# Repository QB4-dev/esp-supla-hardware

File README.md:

# esp-supla-hardware
My SUPLA compatible boards

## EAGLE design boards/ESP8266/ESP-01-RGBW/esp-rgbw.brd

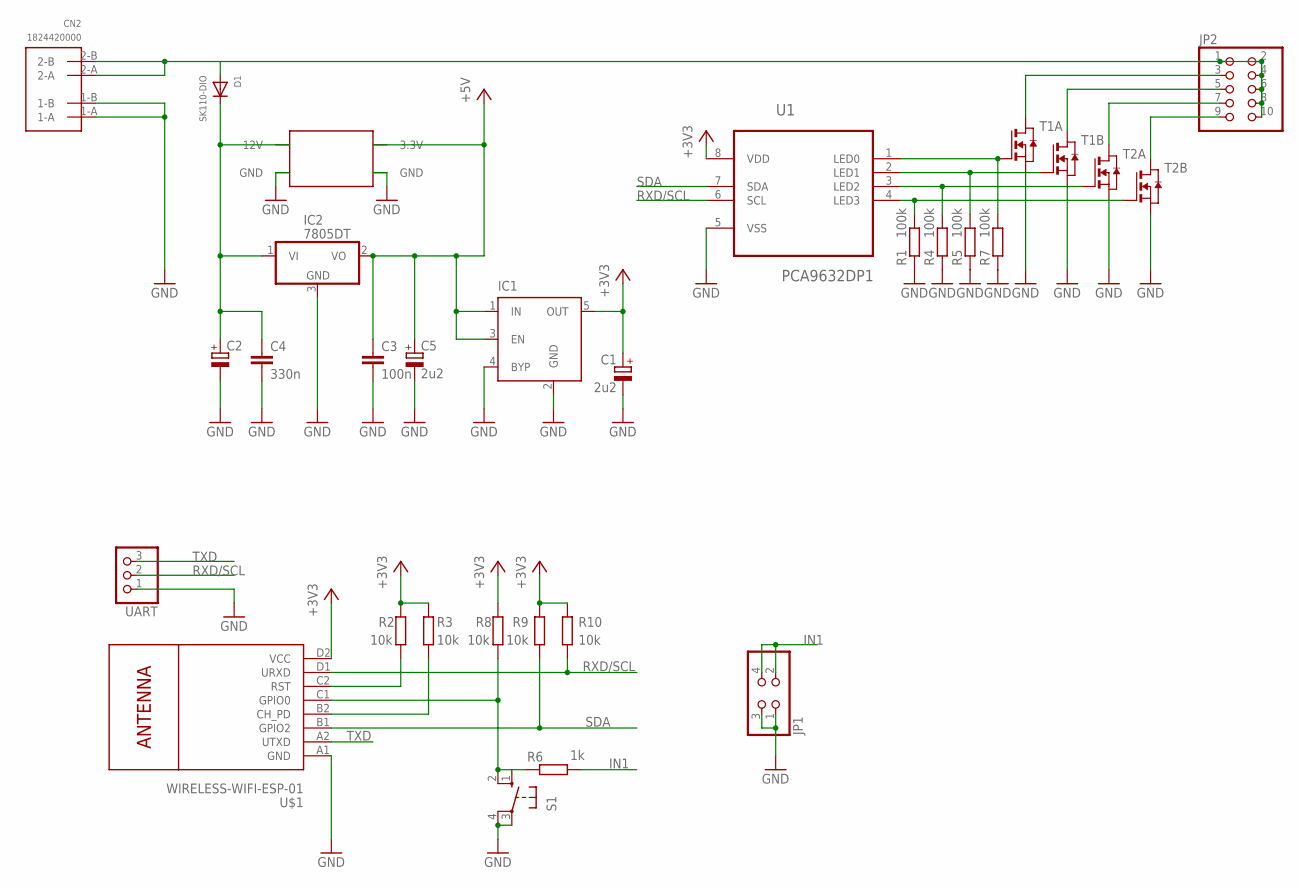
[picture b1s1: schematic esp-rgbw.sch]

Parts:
C1, C5: 2u2; SMC_B
C2: CPOL-EUC/6032-28R; C/6032-28R
C3: 100n; C0805
C4: 330n; C0805
CN2: 1824420000
D1: SK110-DIO; SMADIODE
IC1: MIC5219XX; SOT23-5
IC2: 7805DT; TO252
JP1: PINHD-2X2; 2X02
JP2: PINHD-2X5; 2X05
R1, R4, R5, R7: 100k; R0805
R2, R3, R8, R9, R10: 10k; R0805
R6: 1k; R0805
S1: 10-XX; B3F-10XX
T1, T2: NMOS2SO8; SO8
U1: PCA9632DP1; SOP65P490X110-8N
U$1: WIRELESS-WIFI-ESP-01
U$2: MP2307-MINI-360
UART: PINHD-1X3; 1X03

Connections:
+3V3: C1.+, IC1.5 (OUT), R2.2, R3.2, R8.2, R9.2, R10.2, U1.8 (VDD), U$1.D2 (VCC)
+5V: C3.1, C5.+, IC1.1 (IN), IC1.3 (EN), IC2.2 (VO), U$2.3.3V
GND: C1.-, C2.-, C3.2, C4.2, C5.-, CN2.1-A, CN2.1-B, IC1.2 (GND), IC1.4 (BYP), IC2.3 (GND), JP1.1, JP1.3, R1.1, R4.1, R5.1, R7.1, S1.3, S1.4 (P1), T1.1 (S), T1.3 (S), T2.1 (S), T2.3 (S), U1.5 (VSS), U$1.A1 (GND), U$2.GND@1 (GND), U$2.GND@2 (GND), UART.1
IN1: JP1.2, JP1.4, R6.1
unnamed: R3.1, U$1.B2 (CH_PD)
unnamed: R2.1, U$1.C2 (RST)
unnamed: R6.2, R8.1, S1.1 (S), S1.2 (S1), U$1.C1 (GPIO0)
unnamed: JP2.3, T1.7 (D), T1.8 (D)
unnamed: JP2.5, T1.5 (D), T1.6 (D)
unnamed: C2.+, C4.1, D1.C, IC2.1 (VI), U$2.12V
unnamed: JP2.7, T2.7 (D), T2.8 (D)
unnamed: JP2.9, T2.5 (D), T2.6 (D)
unnamed: R1.2, T2.4 (G), U1.4 (LED3)
unnamed: R4.2, T2.2 (G), U1.3 (LED2)
unnamed: R5.2, T1.4 (G), U1.2 (LED1)
unnamed: R7.2, T1.2 (G), U1.1 (LED0)
OUT+: CN2.2-A, CN2.2-B, D1.A, JP2.1, JP2.2, JP2.4, JP2.6, JP2.8, JP2.10
RXD/SCL: R10.1, U1.6 (SCL), U$1.D1 (URXD), UART.2
SDA: R9.1, U1.7 (SDA), U$1.B1 (GPIO2)
TXD: U$1.A2 (UTXD), UART.3

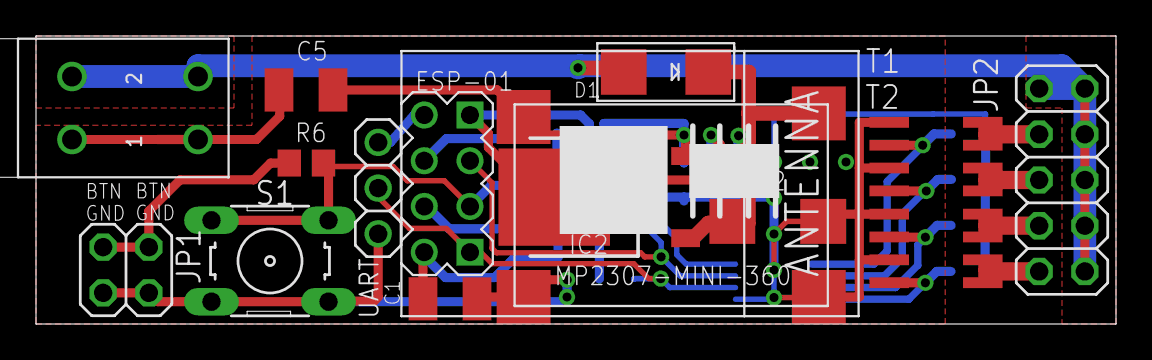
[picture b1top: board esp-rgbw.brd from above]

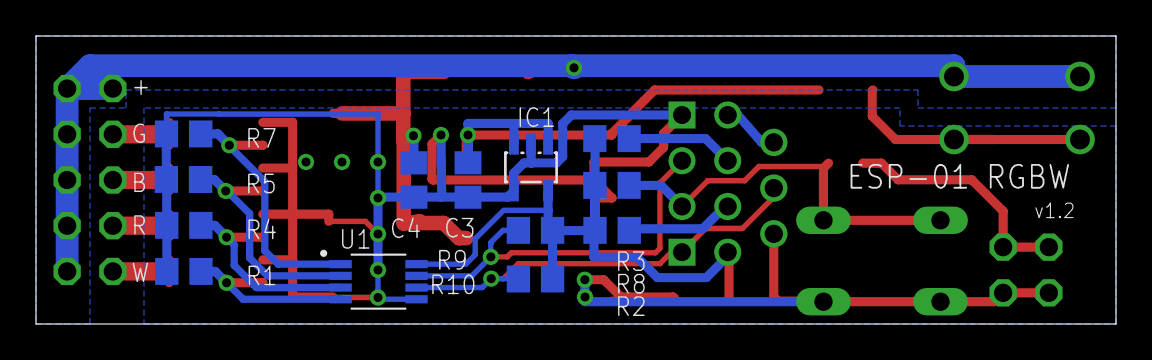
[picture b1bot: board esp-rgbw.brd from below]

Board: 2 copper layers, 60.0 x 16.0 mm, 28 parts (13 on the bottom side), 20 nets.

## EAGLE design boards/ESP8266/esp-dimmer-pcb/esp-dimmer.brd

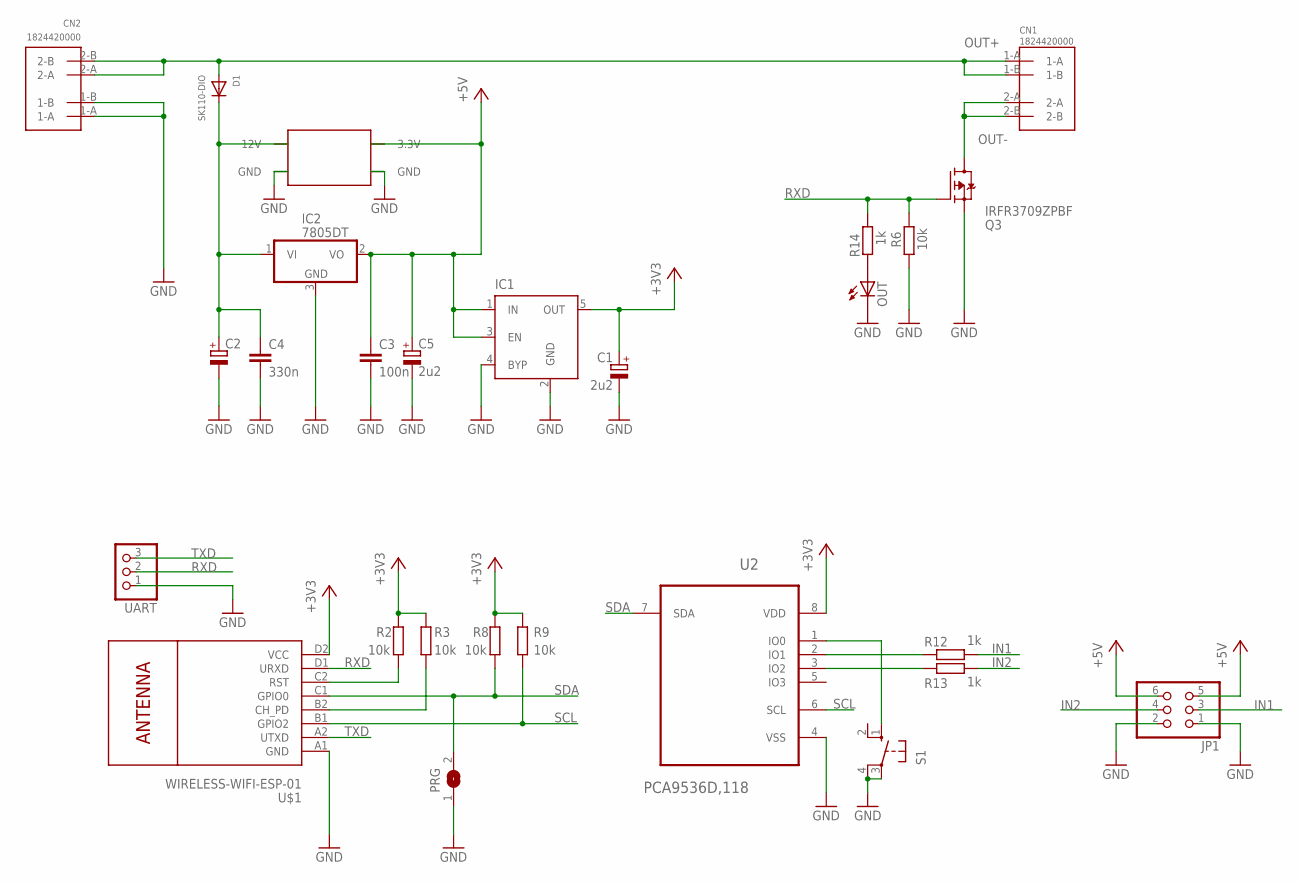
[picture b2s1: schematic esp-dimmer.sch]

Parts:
C1, C5: 2u2; SMC_B
C2: CPOL-EUC/6032-28R; C/6032-28R
C3: 100n; C0805
C4: 330n; C0805
CN1, CN2: 1824420000
D1: SK110-DIO; SMADIODE
IC1: MIC5219XX; SOT23-5
IC2: 7805DT; TO252
JP1: PINHD-2X3; 2X03
OUT: LEDCHIPLED_0805; CHIPLED_0805
PRG: SJ
Q3: IRFR3709ZPBF; TO252
R2, R3, R6, R8, R9: 10k; R0805
R12, R13, R14: 1k; R0805
S1: 10-XX; B3F-10XX
U2: PCA9536D,118; SOIC127P600X175-8N
U$1: WIRELESS-WIFI-ESP-01
U$2: MP2307-MINI-360
UART: PINHD-1X3; 1X03

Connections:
+3V3: C1.+, IC1.5 (OUT), R2.2, R3.2, R8.2, R9.2, U2.8 (VDD), U$1.D2 (VCC)
+5V: C3.1, C5.+, IC1.1 (IN), IC1.3 (EN), IC2.2 (VO), JP1.5, JP1.6, U$2.3.3V
GND: C1.-, C2.-, C3.2, C4.2, C5.-, CN2.1-A, CN2.1-B, IC1.2 (GND), IC1.4 (BYP), IC2.3 (GND), JP1.1, JP1.2, OUT.C, PRG.1, Q3.2 (S), R6.2, S1.3, S1.4 (P1), U2.4 (VSS), U$1.A1 (GND), U$2.GND@1 (GND), U$2.GND@2 (GND), UART.1
IN1: JP1.3, R12.1
IN2: JP1.4, R13.1
unnamed: R3.1, U$1.B2 (CH_PD)
unnamed: R2.1, U$1.C2 (RST)
unnamed: S1.1 (S), U2.1 (IO0)
unnamed: R13.2, U2.3 (IO2)
unnamed: R12.2, U2.2 (IO1)
unnamed: C2.+, C4.1, D1.C, IC2.1 (VI), U$2.12V
unnamed: OUT.A, R14.1
OUT+: CN1.1-A, CN1.1-B, CN2.2-A, CN2.2-B, D1.A
OUT-: CN1.2-A, CN1.2-B, Q3.3 (D)
RXD: Q3.1 (G), R6.1, R14.2, U$1.D1 (URXD), UART.2
SCL: R9.1, U2.6 (SCL), U$1.B1 (GPIO2)
SDA: PRG.2, R8.1, U2.7 (SDA), U$1.C1 (GPIO0)
TXD: U$1.A2 (UTXD), UART.3

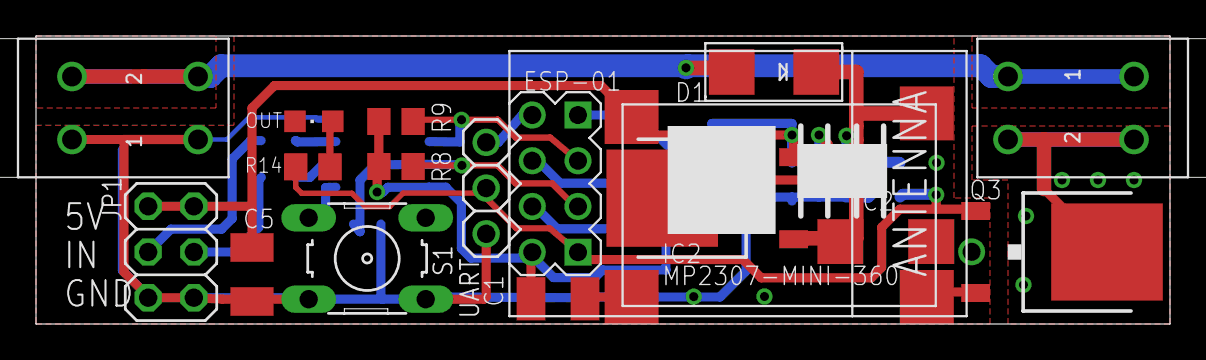
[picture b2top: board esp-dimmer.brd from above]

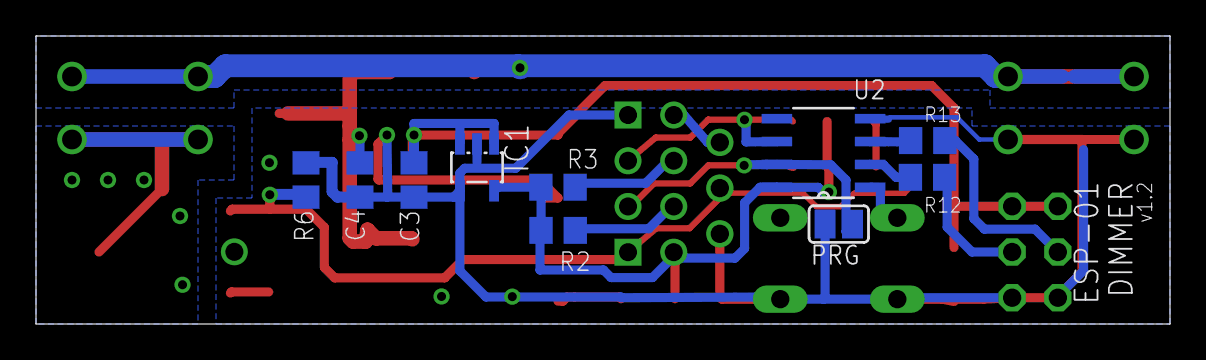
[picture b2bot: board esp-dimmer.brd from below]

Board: 2 copper layers, 63.0 x 16.0 mm, 27 parts (10 on the bottom side), 18 nets.

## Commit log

2024-12-29 added common adoc directory
2024-12-29 added first manual
2024-12-29 DIMMER manual updated
2024-12-29 udpaded manual
2024-12-30 updated manual
2024-12-30 Added boards and schematics
2025-01-04 Renamed pcb dirs
2025-01-04 reordered pdf gen script
2025-01-04 updated pdfs
2025-01-10 reordered common parts

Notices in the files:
parts and their libraries:
diy-modules: Released under the Creative Commons Attribution 4.0 International License: http://creativecommons.org/licenses/by/4.0
